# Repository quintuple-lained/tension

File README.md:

# tension
a b0xx clone with inspiration taken from Bob's Stress board

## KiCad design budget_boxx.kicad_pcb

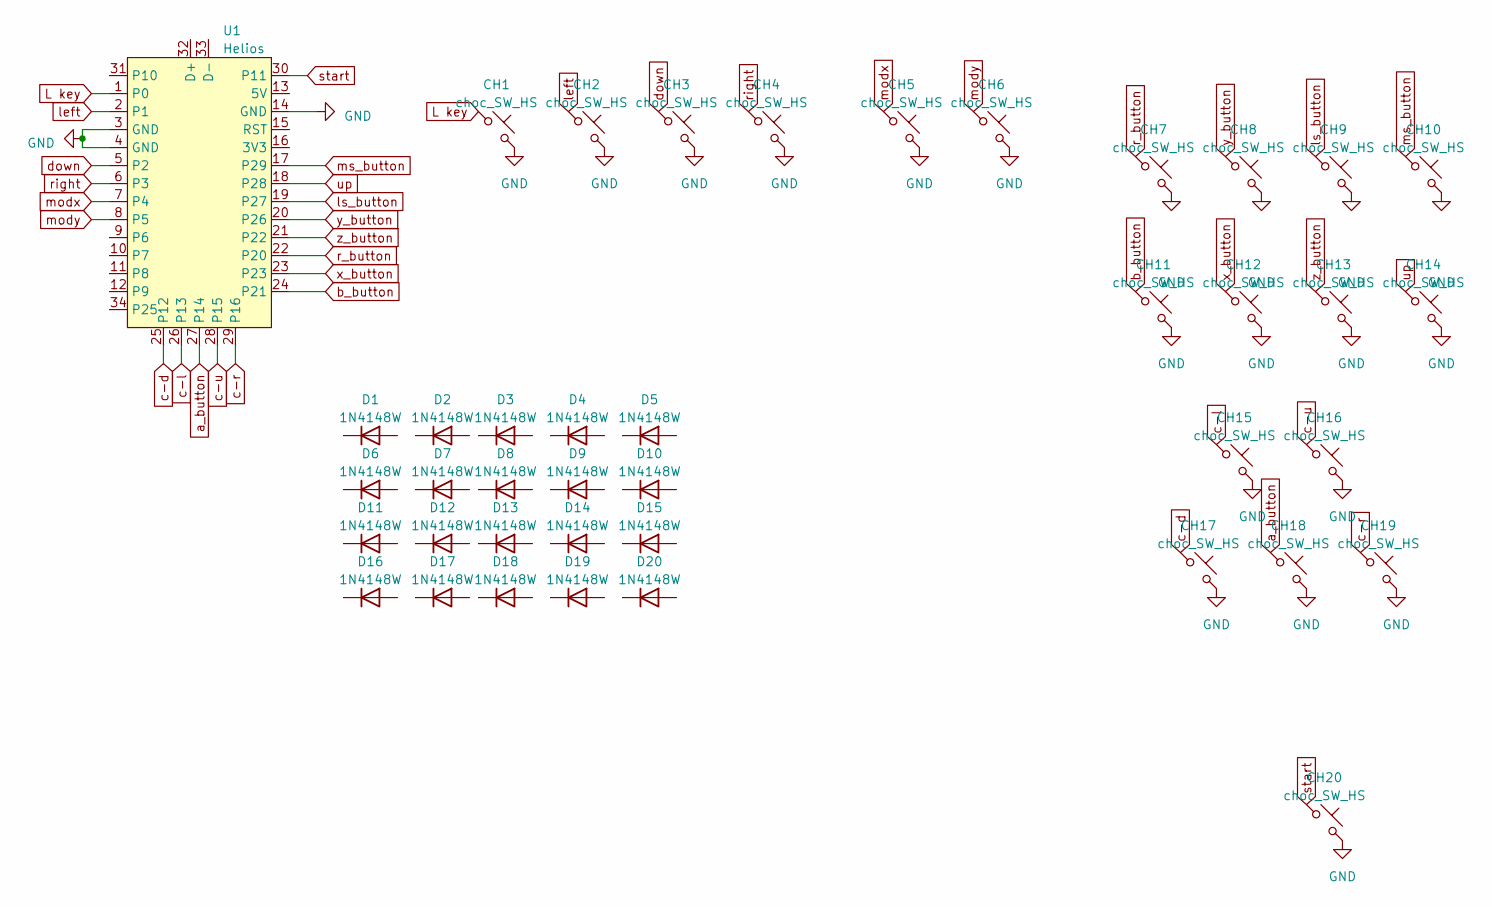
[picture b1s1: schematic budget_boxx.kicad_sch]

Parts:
CH1, CH2, CH3, CH4, CH5, CH6, CH7, CH8, CH9, CH10, CH11, CH12, CH13, CH14, CH15, CH16, CH17, CH18, CH19, CH20: choc_SW_HS; SW_choc_v1_HS_1u
D1, D2, D3, D4, D5, D6, D7, D8, D9, D10, D11, D12, D13, D14, D15, D16, D17, D18, D19, D20: 1N4148W; D_SOD-123
U1: Helios; Helios_AH_USBup

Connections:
GND: CH1.2, CH2.2, CH3.2, CH4.2, CH5.2, CH6.2, CH7.2, CH8.2, CH9.2, CH10.2, CH11.2, CH12.2, CH13.2, CH14.2, CH15.2, CH16.2, CH17.2, CH18.2, CH19.2, CH20.2, U1.3 (GND), U1.4 (GND), U1.14 (GND)
L key: CH1.1, U1.1 (P0)
a_button: CH18.1, U1.27 (P14)
b_button: CH11.1, U1.24 (P21)
c-d: CH17.1, U1.25 (P12)
c-l: CH15.1, U1.26 (P13)
c-r: CH19.1, U1.29 (P16)
c-u: CH16.1, U1.28 (P15)
down: CH3.1, U1.5 (P2)
left: CH2.1, U1.2 (P1)
ls_button: CH9.1, U1.19 (P27)
modx: CH5.1, U1.7 (P4)
mody: CH6.1, U1.8 (P5)
ms_button: CH10.1, U1.17 (P29)
r_button: CH7.1, U1.22 (P20)
right: CH4.1, U1.6 (P3)
start: CH20.1, U1.30 (P11)
up: CH14.1, U1.18 (P28)
x_button: CH12.1, U1.23
y_button: CH8.1, U1.20 (P26)
z_button: CH13.1, U1.21 (P22)

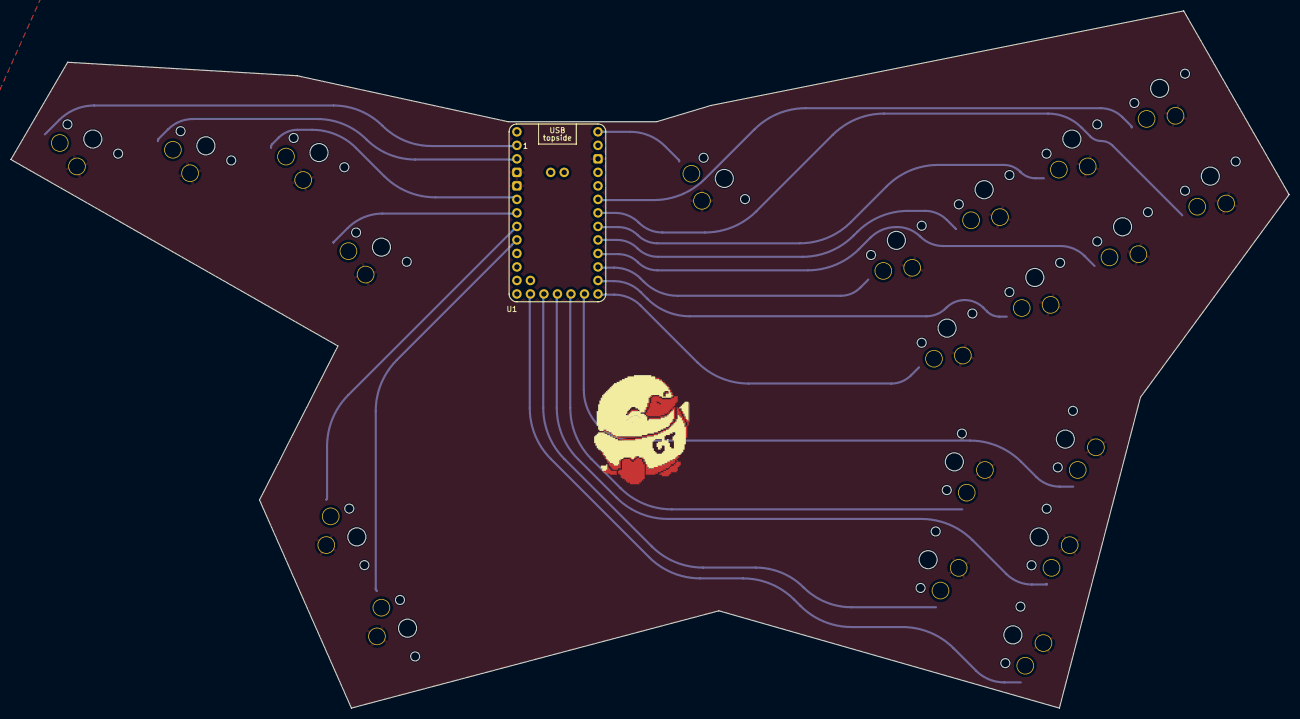
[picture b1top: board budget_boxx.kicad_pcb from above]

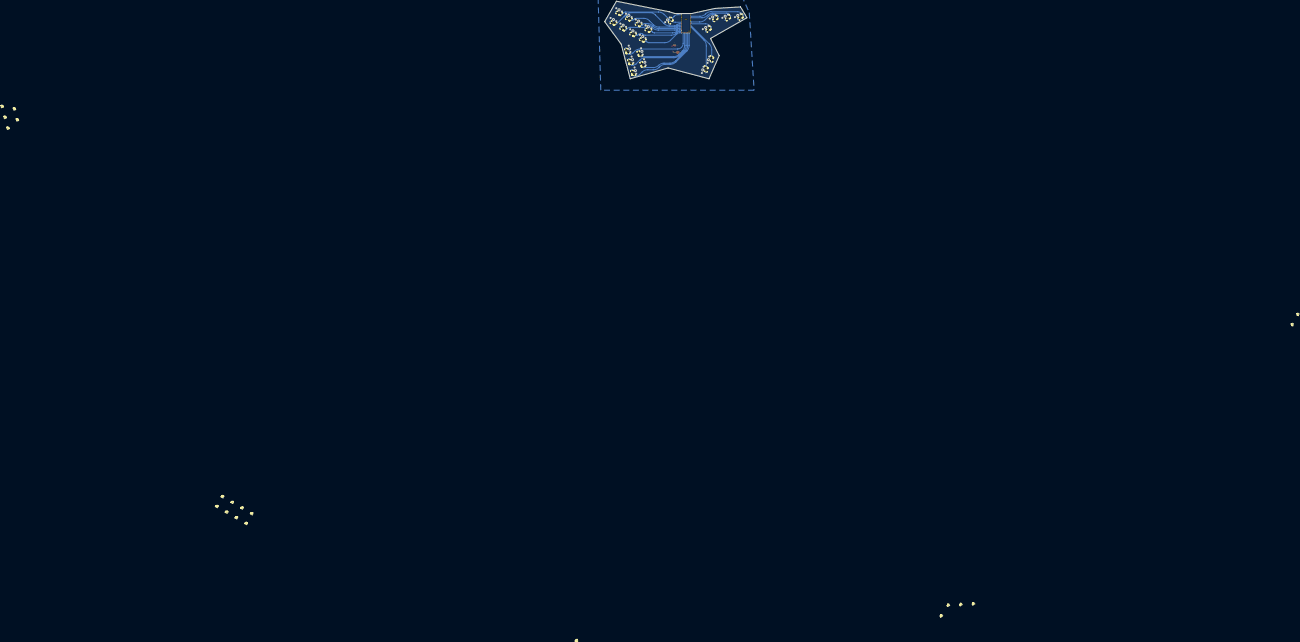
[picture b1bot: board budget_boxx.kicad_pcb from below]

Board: 2 copper layers, 240.3 x 131.1 mm, 41 parts (40 on the bottom side), 21 nets.

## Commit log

2024-02-21 added files
